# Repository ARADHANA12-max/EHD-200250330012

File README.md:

# EHD-200250330012
DESD Embedded Hardware Assignments

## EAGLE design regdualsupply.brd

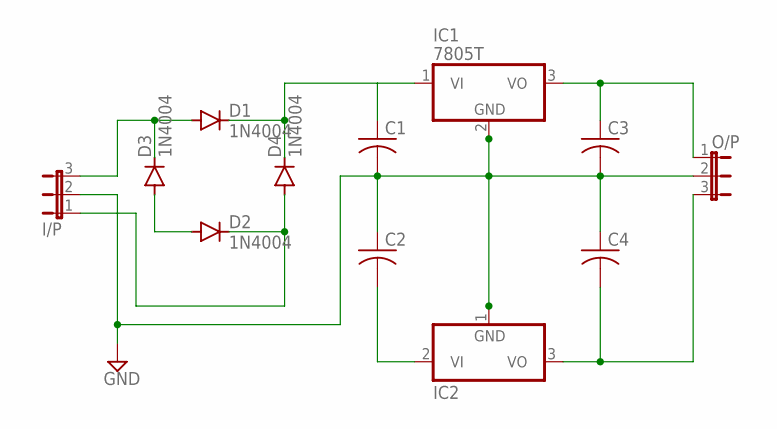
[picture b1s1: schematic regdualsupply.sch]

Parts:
C1, C2, C3, C4: C-US025-025X050; C025-025X050
D1, D2, D3, D4: 1N4004; DO41-10
I/P: JP2W
IC1: 7805T; TO220H
IC2: 7905T; TO220H
O/P: JP2W

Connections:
GND: C1.2, C2.1, C3.2, C4.1, I/P.2, IC1.2 (GND), IC2.1 (GND), O/P.2
unnamed: C1.1, D1.C, D4.C, IC1.1 (VI)
unnamed: D1.A, D3.C, I/P.3
unnamed: C3.1, IC1.3 (VO), O/P.1
unnamed: D2.A, D3.A
unnamed: C2.2, IC2.2 (VI)
unnamed: C4.2, IC2.3 (VO), O/P.3
unnamed: D2.C, D4.A, I/P.1

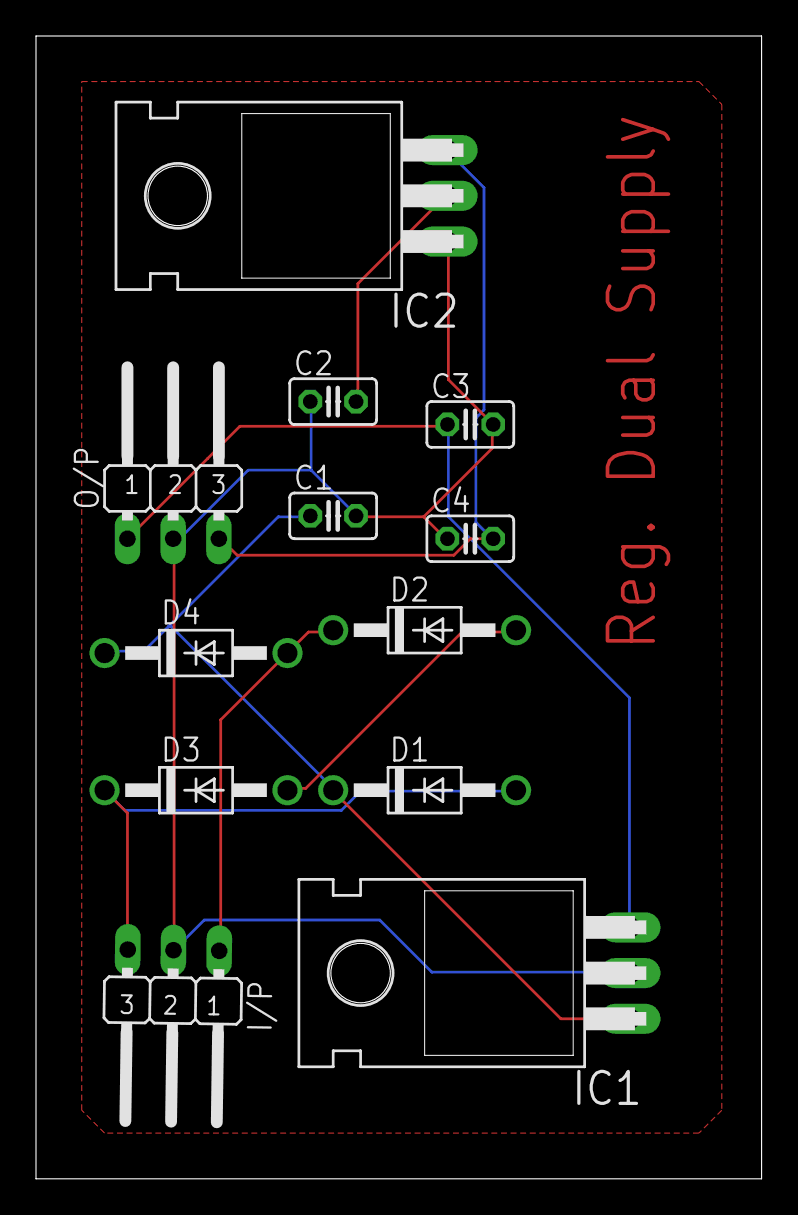
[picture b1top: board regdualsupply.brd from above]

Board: 2 copper layers, 40.3 x 63.5 mm, 12 parts (0 on the bottom side), 8 nets.

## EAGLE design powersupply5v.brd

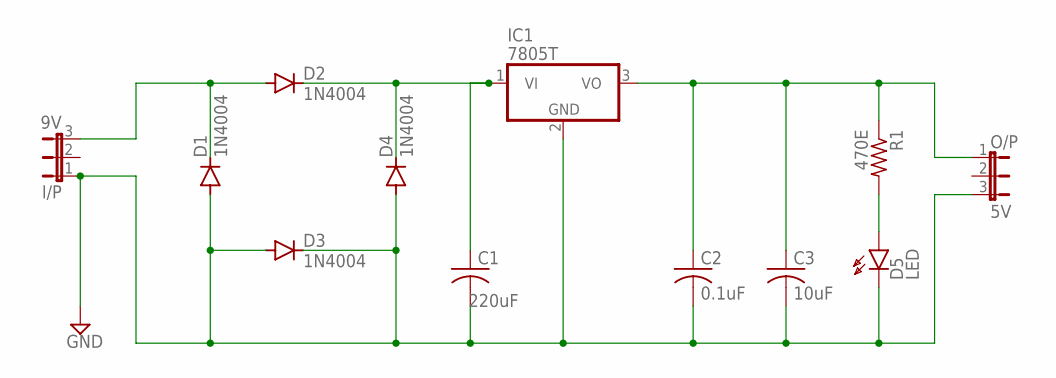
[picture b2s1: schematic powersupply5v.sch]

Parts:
C1: 220uF; C025-024X044
C2: 0.1uF; C025-024X044
C3: 10uF; C025-024X044
D1, D2, D3, D4: 1N4004; DO41-10
D5: LED; HLMP6
I/P: 9V; JP2W
IC1: 7805T; TO220H
O/P: 5V; JP2W
R1: 470E; 0204V

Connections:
GND: C1.2, C2.2, C3.2, D1.A, D3.A, D3.C, D4.A, D5.K, I/P.1, IC1.2 (GND), O/P.3
unnamed: C1.1, D2.C, D4.C, IC1.1 (VI)
unnamed: D1.C, D2.A, I/P.3
unnamed: C2.1, C3.1, IC1.3 (VO), O/P.1, R1.1
unnamed: D5.A, R1.2

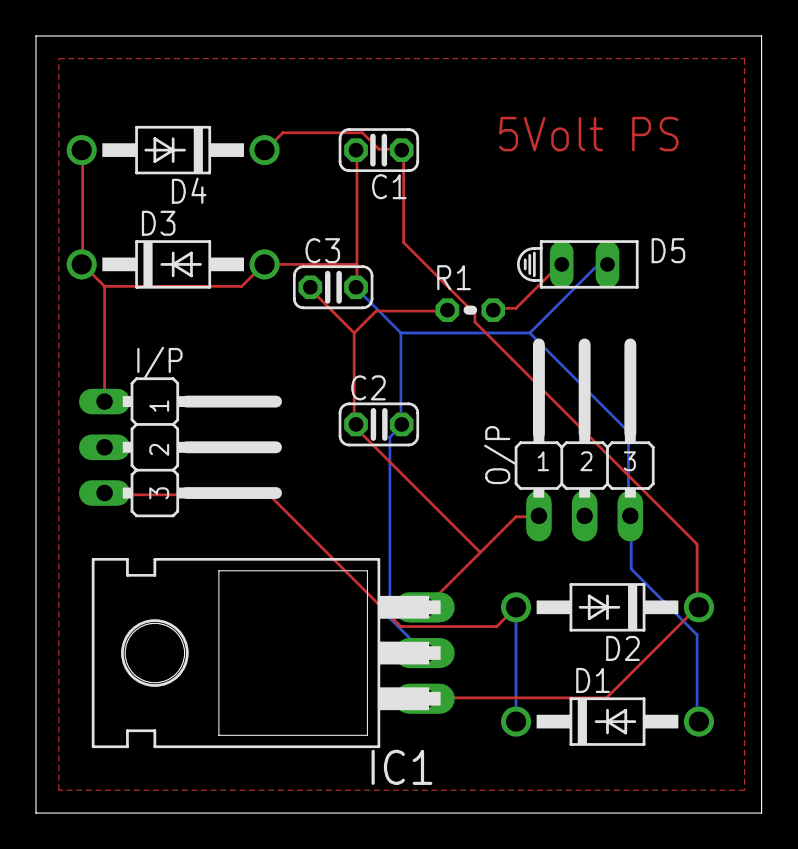
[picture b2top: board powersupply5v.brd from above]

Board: 2 copper layers, 40.3 x 43.2 mm, 12 parts (0 on the bottom side), 5 nets.
